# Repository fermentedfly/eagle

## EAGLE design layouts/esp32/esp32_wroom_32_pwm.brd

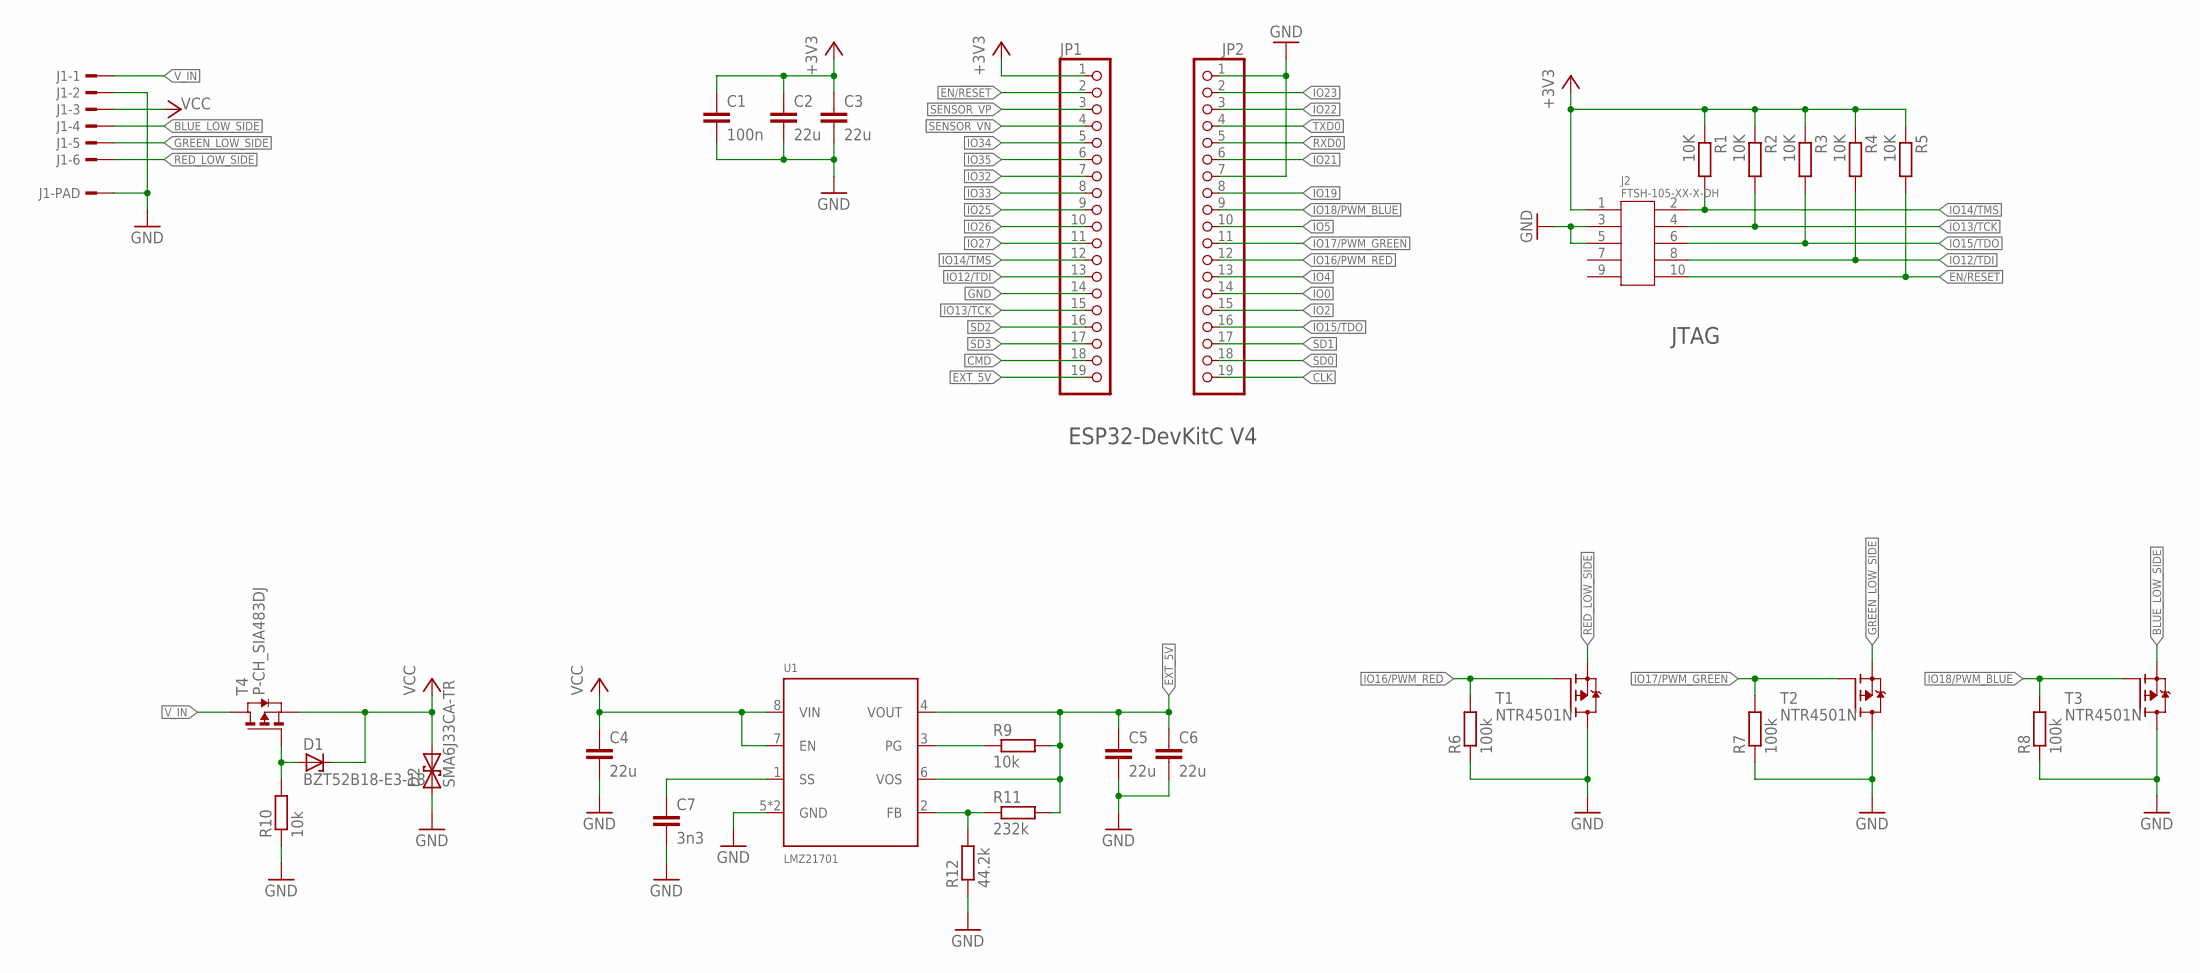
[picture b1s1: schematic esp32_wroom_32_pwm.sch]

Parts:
C1: 100n; C0603
C2, C3, C4, C5, C6: 22u; C1210
C7: 3n3; C0603
D1: BZT52B18-E3-18; SOD123F
D2: SMA6J33CA-TR; DO214AC
J1: 292227-6
J2: FTSH-105-XX-X-DH; FTSH-105-XX-XXX-DH
JP1, JP2: PINHD-1X19; 1X19
R1, R2, R3, R4, R5: 10K; R0603
R6, R7, R8: 100k; R0603
R9, R10: 10k; R0603
R11: 232k; R0603
R12: 44.2k; R0603
T1, T2, T3: NTR4501N; SOT23
T4: P-CH_SIA483DJ; POWERPAK_SC70-6L
U1: LMZ21701; SIL0008E

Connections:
+3V3: C1.1, C2.1, C3.1, J2.1, JP1.1, R1.1, R2.1, R3.1, R4.1, R5.1
BLUE_LOW_SIDE: J1.4, T3.2 (S)
CLK: JP2.19
CMD: JP1.18
EN/!RESET: J2.10, JP1.2, R5.2
EXT_5V: C5.1, C6.1, JP1.19, R9.2, R11.2, U1.4 (VOUT), U1.6 (VOS)
GND: C1.2, C2.2, C3.2, C4.2, C5.2, C6.2, C7.2, D2.A (1), J1.2, J1.PAD1, J1.PAD2, J2.3, J2.5, JP1.14, JP2.1, JP2.7, R6.1, R7.1, R8.1, R10.1, R12.1, T1.3 (D), T2.3 (D), T3.3 (D), U1.5 (GND), U1.PAD (GND)
GREEN_LOW_SIDE: J1.5, T2.2 (S)
IO0: JP2.14
IO2: JP2.15
IO4: JP2.13
IO5: JP2.10
IO12/TDI: J2.8, JP1.13, R4.2
IO13/TCK: J2.4, JP1.15, R2.2
IO14/TMS: J2.2, JP1.12, R1.2
IO15/TDO: J2.6, JP2.16, R3.2
IO16/PWM_RED: JP2.12, R6.2, T1.1 (G)
IO17/PWM_GREEN: JP2.11, R7.2, T2.1 (G)
IO18/PWM_BLUE: JP2.9, R8.2, T3.1 (G)
IO19: JP2.8
IO21: JP2.6
IO22: JP2.3
IO23: JP2.2
IO25: JP1.9
IO26: JP1.10
IO27: JP1.11
IO32: JP1.7
IO33: JP1.8
IO34: JP1.5
IO35: JP1.6
LMZ_FB: R11.1, R12.2, U1.2 (FB)
LMZ_PG: R9.1, U1.3 (PG)
LMZ_SS: C7.1, U1.1 (SS)
unnamed: D1.A, R10.2, T4.3 (G)
RED_LOW_SIDE: J1.6, T1.2 (S)
RXD0: JP2.5
SD0: JP2.18
SD1: JP2.17
SD2: JP1.16
SD3: JP1.17
SENSOR_VN: JP1.4
SENSOR_VP: JP1.3
TXD0: JP2.4
VCC: C4.1, D1.C, D2.C (2), J1.3, T4.4 (S), T4.TH_S (S), U1.7 (EN), U1.8 (VIN)
V_IN: J1.1, T4.1 (D), T4.2 (D), T4.5 (D), T4.6 (D), T4.TH_D (D)

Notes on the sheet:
ESP32-DevKitC V4
JTAG

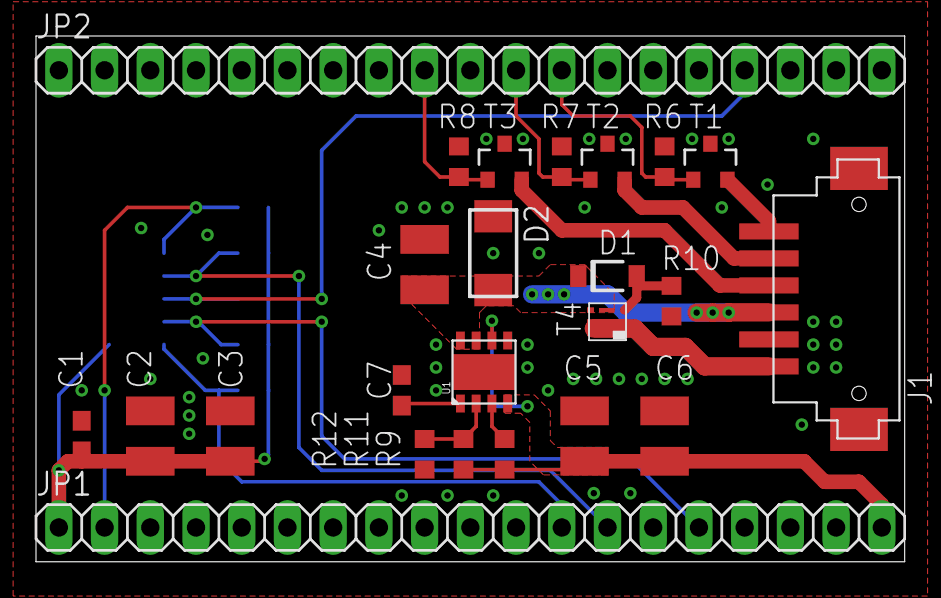
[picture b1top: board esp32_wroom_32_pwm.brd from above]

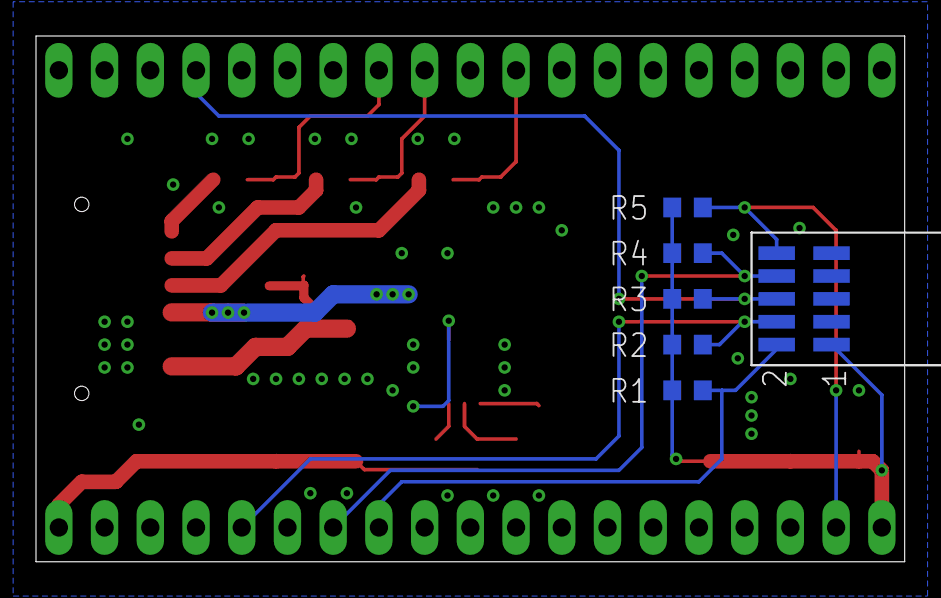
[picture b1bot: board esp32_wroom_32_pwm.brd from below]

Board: 2 copper layers, 48.3 x 29.2 mm, 30 parts (6 on the bottom side), 20 nets.

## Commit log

2018-11-23 cleanup in libraries
2018-11-23 fixed stop layer for vias
2018-11-23 added all layout not belonging to other projects
2018-11-23 added diode library + p fet for reverse voltage protection
2019-08-21 added distributor / order_code attr set ulp
2019-08-22 distributor attr script now supports multiple parts
2019-08-22 fixed bad string comparison
2019-09-06 added esp32 pwm breakout
